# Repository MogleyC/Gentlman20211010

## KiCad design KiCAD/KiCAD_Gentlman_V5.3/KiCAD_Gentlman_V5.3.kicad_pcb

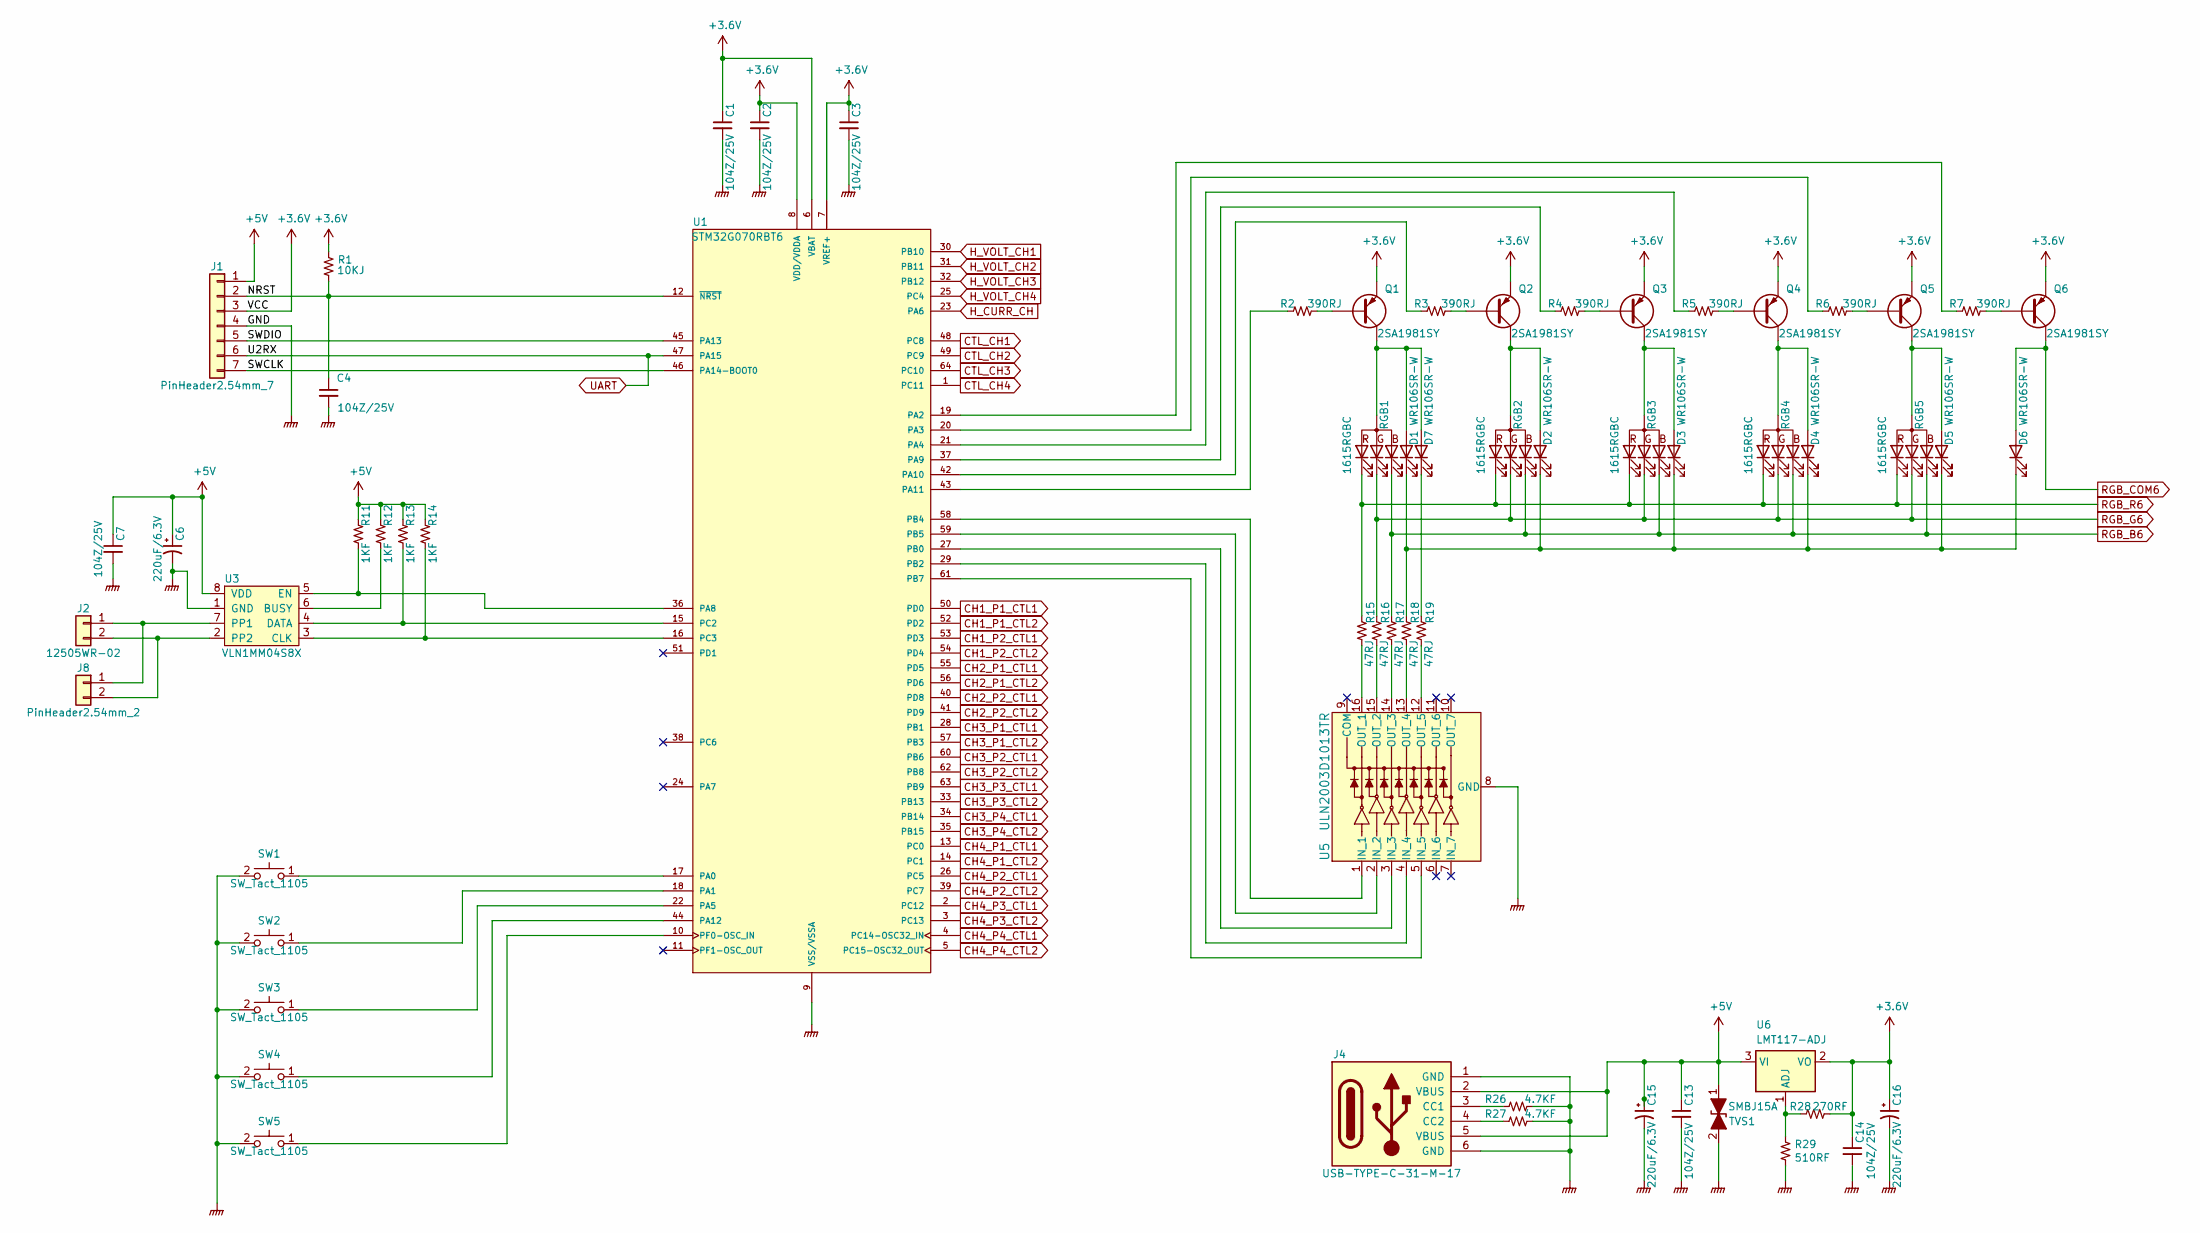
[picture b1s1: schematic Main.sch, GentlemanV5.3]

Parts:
C1, C2, C3, C4, C7, C13, C14: CAP_104Z_25V_1608; C_0603_1608Metric; PartName 104Z/25V
C6, C15, C16: CAP_220uF_6.3V_SC6.3X5.8; C_Elec_6.3x5.8; PartName 220uF/6.3V
CN1: PinHeader2.54mm_7; PinHeader_1x07_P2.54mm_Vertical; PartName PinHeader2.54mm-7P
CN2: 12505WR-02; PartName 12505WR-02
D1, D2, D3, D4, D5, D6, D7: WR106SR-W; LED_0603_1608Metric; PartName WR106SR-W
J4: USB-TYPE-C-31-M-17; TYPE-C-31-M-17-1; PartName USB-TYPE-C-31-M-17
J8: PinHeader2.54mm_2; PinHeader_1x02_P2.54mm_Vertical; PartName PinHeader2.54mm_2
Q1, Q2, Q3, Q4, Q5, Q6: 2SA1981SY; SOT-23; PartName 2SA1981SY
R1: R_10KJ; R_0603_1608Metric; PartName 10KJ
R2, R3, R4, R5, R6, R7: R_390RJ; R_0603_1608Metric; PartName 390RJ
R11, R12, R13, R14: R_1KF; R_0603_1608Metric; PartName 1KF
R15, R16, R17, R18, R19: R_47RJ; R_0603_1608Metric; PartName 47RJ
R26, R27: R_4.7KF; R_0603_1608Metric; PartName 4.7KF
R28: R_270RF; R_0603_1608Metric; PartName 270RF
R29: R_510RF; R_0603_1608Metric; PartName 510RF
RGB1, RGB2, RGB3, RGB4, RGB5: 1615RGBC; LED_RGB_0605; PartName 1615RGBC
SW1, SW2, SW3, SW4, SW5: SW_Tact_1105; SW_PUSH_6mm_H5mm; PartName ITS-1105-5mm
TVS1: SMBJ15A; D_SMB; PartName SMBJ15A
U1: STM32G070RBT6; LQFP-64_10x10mm_P0.5mm; PartName STM32G070RBT6
U3: VLN1MM04S8X; SOP-8_3.76x4.96mm_P1.27mm; PartName VLN1MM04S8X
U5: ULN2003D1013TR; SOIC-16_3.9x9.9mm_P1.27mm; PartName ULN2003D1013TR
U6: LMT117-ADJ; SOT-223-3_TabPin2; PartName LMT117-ADJ

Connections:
+3.6V: C1.1, C2.1, C3.1, C14.1, C16.1, Q1.2 (E), Q2.2 (E), Q3.2 (E), Q4.2 (E), Q5.2 (E), Q6.2 (E), R1.1, R28.1, U1.6 (VBAT), U1.7 (VREF+), U1.8 (VDD/VDDA), U6.2 (VO); also elsewhere on the board
+5V: C6.1, C7.1, C13.1, C15.1, J4.2 (VBUS), J4.5 (VBUS), R11.1, R12.1, R13.1, R14.1, TVS1.1 (A1), U3.8 (VDD), U6.3 (VI); also elsewhere on the board
/Main/NRST: C4.1, R1.2, U1.12 (~NRST); also elsewhere on the board
/Main/SWCLK: U1.46 (PA14-BOOT0); also elsewhere on the board
/Main/SWDIO: U1.45 (PA13); also elsewhere on the board
CH1_P1_CTL1: U1.50 (PD0); also elsewhere on the board
CH1_P1_CTL2: U1.52 (PD2); also elsewhere on the board
CH1_P2_CTL1: U1.53 (PD3); also elsewhere on the board
CH1_P2_CTL2: U1.54 (PD4); also elsewhere on the board
CH2_P1_CTL1: U1.55 (PD5); also elsewhere on the board
CH2_P1_CTL2: U1.56 (PD6); also elsewhere on the board
CH2_P2_CTL1: U1.40 (PD8); also elsewhere on the board
CH2_P2_CTL2: U1.41 (PD9); also elsewhere on the board
CH3_P1_CTL1: U1.28 (PB1); also elsewhere on the board
CH3_P1_CTL2: U1.57 (PB3); also elsewhere on the board
CH3_P2_CTL1: U1.60 (PB6); also elsewhere on the board
CH3_P2_CTL2: U1.62 (PB8); also elsewhere on the board
CH3_P3_CTL1: U1.63 (PB9); also elsewhere on the board
CH3_P3_CTL2: U1.33 (PB13); also elsewhere on the board
CH3_P4_CTL1: U1.34 (PB14); also elsewhere on the board
CH3_P4_CTL2: U1.35 (PB15); also elsewhere on the board
CH4_P1_CTL1: U1.13 (PC0); also elsewhere on the board
CH4_P1_CTL2: U1.14 (PC1); also elsewhere on the board
CH4_P2_CTL1: U1.26 (PC5); also elsewhere on the board
CH4_P2_CTL2: U1.39 (PC7); also elsewhere on the board
CH4_P3_CTL1: U1.2 (PC12); also elsewhere on the board
CH4_P3_CTL2: U1.3 (PC13); also elsewhere on the board
CH4_P4_CTL1: U1.4 (PC14-OSC32_IN); also elsewhere on the board
CH4_P4_CTL2: U1.5 (PC15-OSC32_OUT); also elsewhere on the board
CTL_CH1: U1.48 (PC8); also elsewhere on the board
CTL_CH2: U1.49 (PC9); also elsewhere on the board
CTL_CH3: U1.64 (PC10); also elsewhere on the board
CTL_CH4: U1.1 (PC11); also elsewhere on the board
GNDPWR: C1.2, C2.2, C3.2, C4.2, C6.2, C7.2, C13.2, C14.2, C15.2, C16.2, J4.1 (GND), J4.6 (GND), R26.1, R27.1, R29.2, SW1.2, SW2.2, SW3.2, SW4.2, SW5.2, TVS1.2 (A2), U1.9 (VSS/VSSA), U3.1 (GND), U5.8 (GND); also elsewhere on the board
H_CURR_CH: U1.23 (PA6); also elsewhere on the board
H_VOLT_CH1: U1.30 (PB10); also elsewhere on the board
H_VOLT_CH2: U1.31 (PB11); also elsewhere on the board
H_VOLT_CH3: U1.32 (PB12); also elsewhere on the board
H_VOLT_CH4: U1.25 (PC4); also elsewhere on the board
unnamed: D1.1 (K), D2.1 (K), D3.1 (K), D4.1 (K), D5.1 (K), D6.1 (K), R18.1
unnamed: D1.2 (A), D7.2 (A), Q1.3 (C), RGB1.4 (A)
unnamed: D2.2 (A), Q2.3 (C), RGB2.4 (A)
unnamed: D3.2 (A), Q3.3 (C), RGB3.4 (A)
unnamed: D4.2 (A), Q4.3 (C), RGB4.4 (A)
unnamed: D5.2 (A), Q5.3 (C), RGB5.4 (A)
unnamed: D7.1 (K), R19.1
unnamed 80: J8.1, U3.7 (PP1); also elsewhere on the board
unnamed 81: J8.2, U3.2 (PP2); also elsewhere on the board
unnamed: J4.3 (CC1), R26.2
unnamed: J4.4 (CC2), R27.2
unnamed: Q1.1 (B), R2.1
unnamed: Q2.1 (B), R3.1
unnamed: Q3.1 (B), R4.1
unnamed: Q4.1 (B), R5.1
unnamed: Q5.1 (B), R6.1
unnamed: Q6.1 (B), R7.1
unnamed: R2.2, U1.43 (PA11)
unnamed: R3.2, U1.42 (PA10)
unnamed: R4.2, U1.37 (PA9)
unnamed: R5.2, U1.21 (PA4)
unnamed: R6.2, U1.20 (PA3)
unnamed: R7.2, U1.19 (PA2)
unnamed: R11.2, U1.36 (PA8), U3.5 (EN)
unnamed: R12.2, U3.6 (BUSY)
unnamed: R13.2, U1.15 (PC2), U3.4 (DATA)
unnamed: R14.2, U1.16 (PC3), U3.3 (CLK)
unnamed: R15.2, U5.16 (OUT_1)
unnamed: R16.2, U5.15 (OUT_2)
unnamed: R17.2, U5.14 (OUT_3)
unnamed: R18.2, U5.13 (OUT_4)
unnamed: R19.2, U5.12 (OUT_5)
unnamed: R28.2, R29.1, U6.1 (ADJ)
unnamed: SW1.1, U1.17 (PA0)
unnamed: SW2.1, U1.18 (PA1)
unnamed: SW3.1, U1.22 (PA5)
unnamed: SW4.1, U1.44 (PA12)
unnamed: SW5.1, U1.10 (PF0-OSC_IN)
unnamed: U1.27 (PB0), U5.3 (IN_3)
unnamed: U1.29 (PB2), U5.4 (IN_4)
unnamed: U1.58 (PB4), U5.1 (IN_1)
unnamed: U1.59 (PB5), U5.2 (IN_2)
unnamed: U1.61 (PB7), U5.5 (IN_5)
RGB_B6: R17.1, RGB1.3 (BK), RGB2.3 (BK), RGB3.3 (BK), RGB4.3 (BK), RGB5.3 (BK); also elsewhere on the board
RGB_COM6: D6.2 (A), Q6.3 (C); also elsewhere on the board
RGB_G6: R16.1, RGB1.2 (GK), RGB2.2 (GK), RGB3.2 (GK), RGB4.2 (GK), RGB5.2 (GK); also elsewhere on the board
RGB_R6: R15.1, RGB1.1 (RK), RGB2.1 (RK), RGB3.1 (RK), RGB4.1 (RK), RGB5.1 (RK); also elsewhere on the board
UART: U1.47 (PA15); also elsewhere on the board

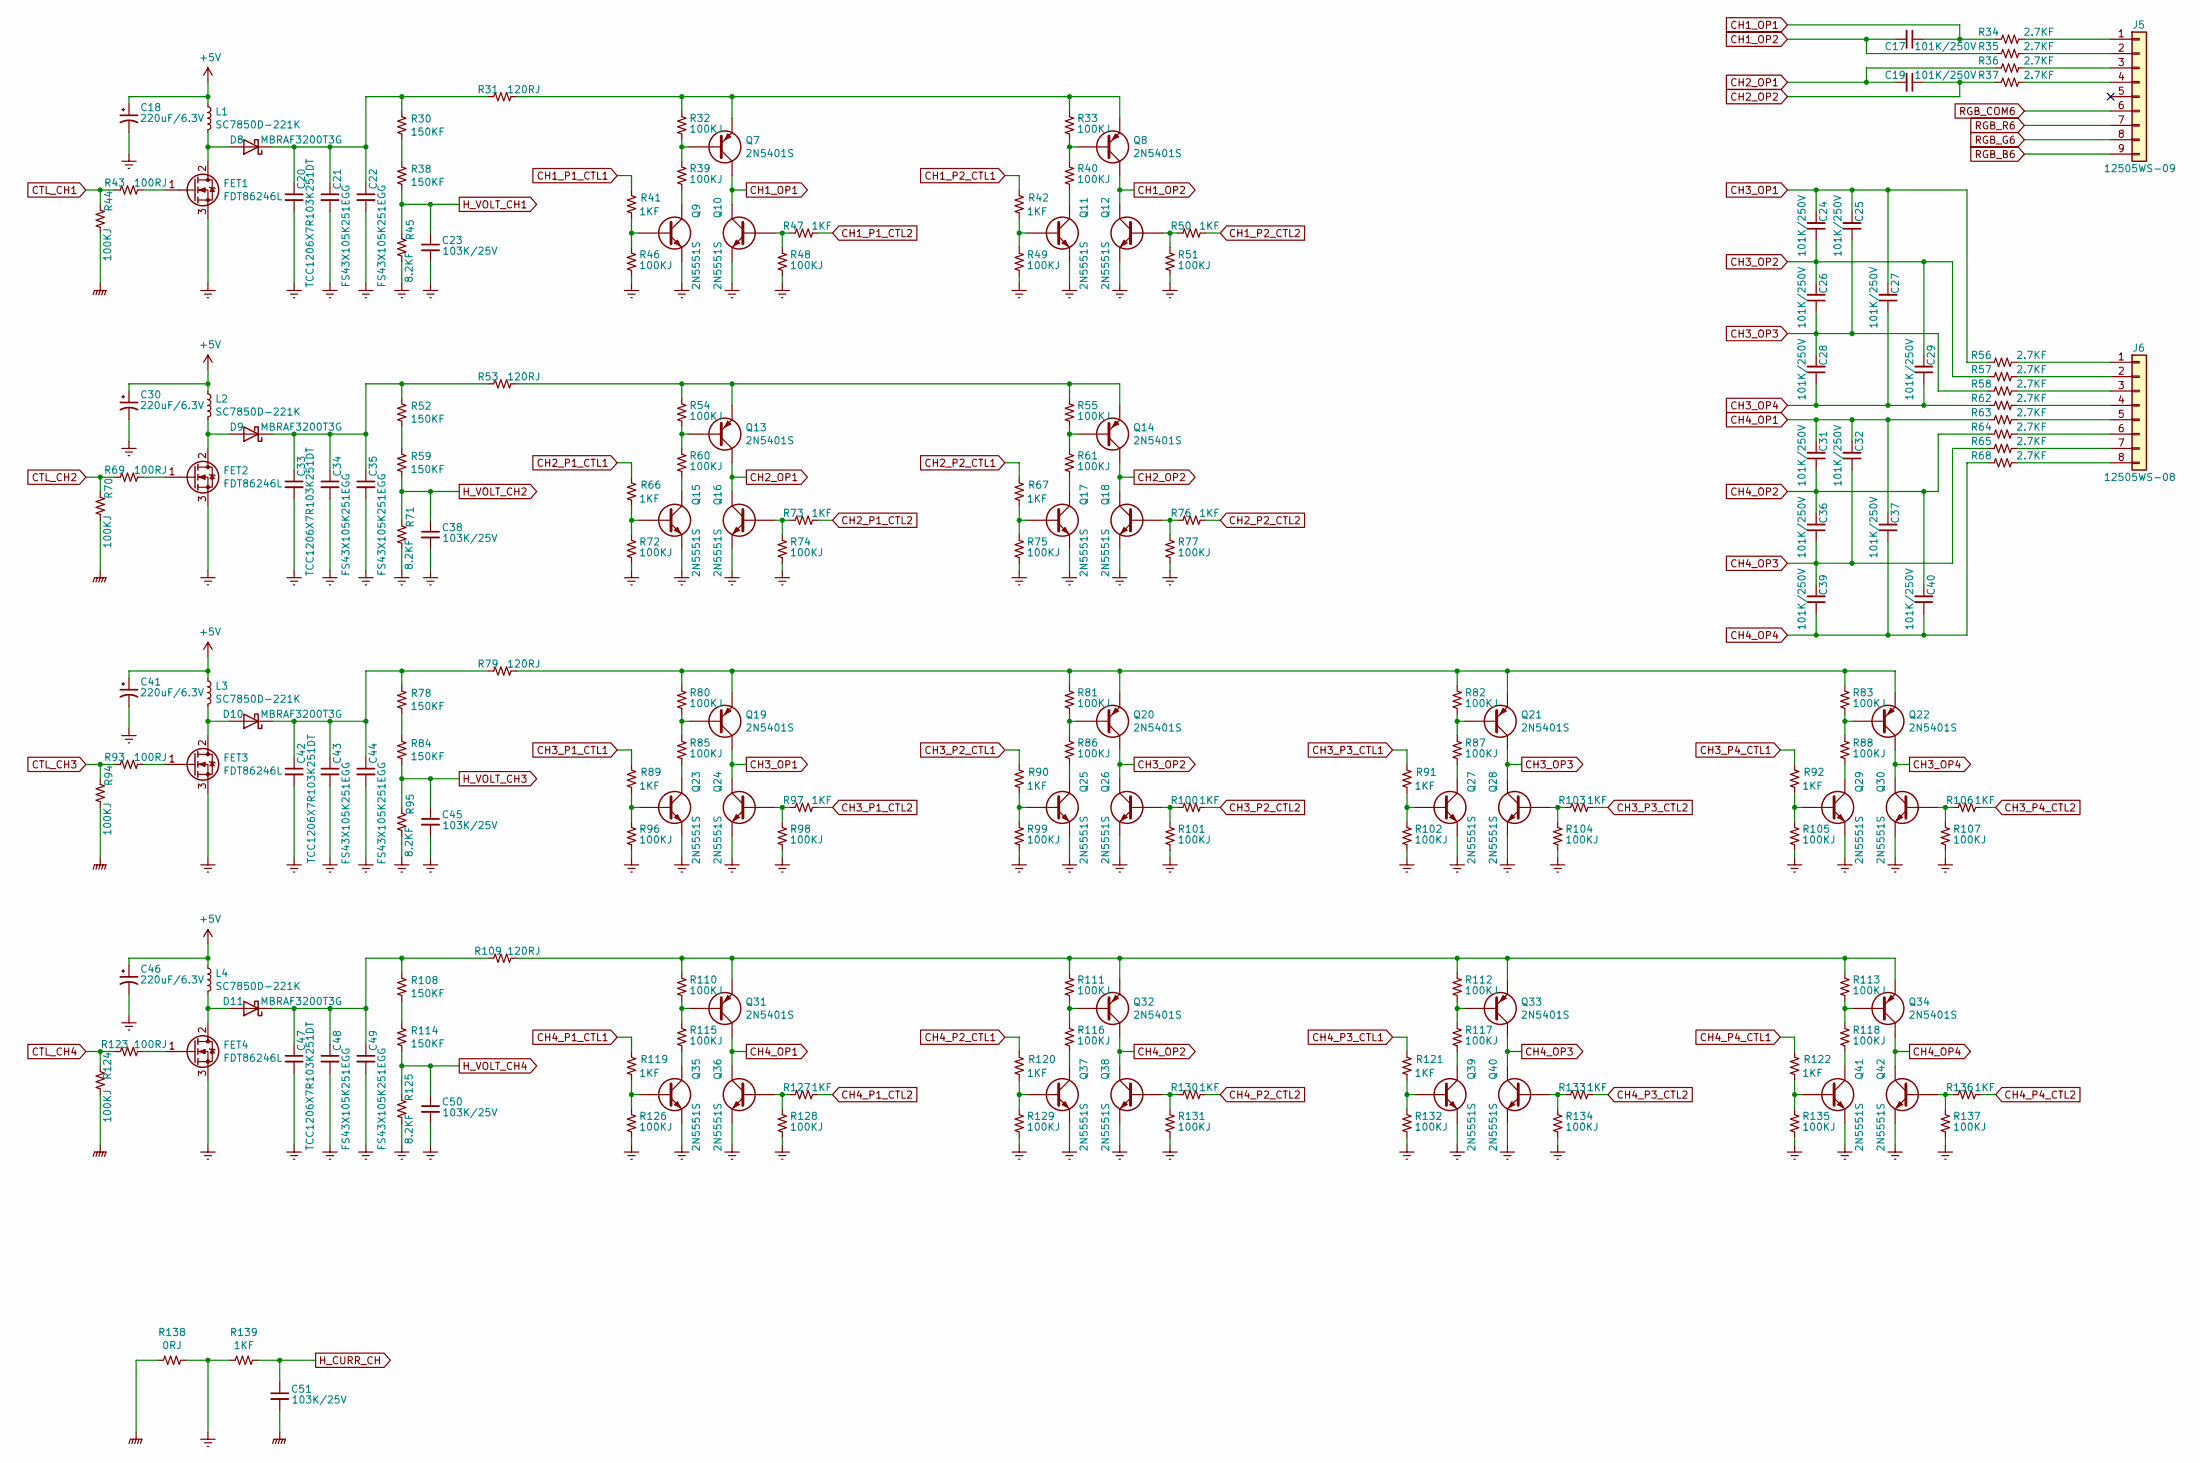
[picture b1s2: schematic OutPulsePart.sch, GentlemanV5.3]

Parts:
C17, C19, C24, C25, C26, C27, C28, C29, C31, C32, C36, C37, C39, C40: CAP_101K_250V_2012; C_0805_2012Metric; PartName 101K/250V
C18, C30, C41, C46: CAP_220uF_6.3V_SC6.3X5.8; C_Elec_6.3x5.8; PartName 220uF/6.3V
C20, C33, C42, C47: CAP_103K_250V_3216; C_1206_3216Metric; PartName TCC1206X7R103K251DT
C21, C22, C34, C35, C43, C44, C48, C49: CAP_105K_250V_4532; C_1812_4532Metric; PartName FS43X105K251EGG
C23, C38, C45, C50, C51: CAP_103K_25V_1608; C_0603_1608Metric; PartName 103K/25V
D8, D9, D10, D11: MBRAF3200T3G; D_SMA; PartName MBRAF3200T3G
FET1, FET2, FET3, FET4: FDT86246L; SOT-223-3_TabPin2; PartName FDT86246L
J5: 12505WS-09; PartName 12505WS-09
J6: 12505WS-08; PartName 12505WS-08
L1, L2, L3, L4: SC7850D-221K; L_SC7850D-221K; PartName SC7850D-221K
Q7, Q8, Q13, Q14, Q19, Q20, Q21, Q22, Q31, Q32, Q33, Q34: 2N5401S; SOT-23; PartName 2N5401S
Q9, Q10, Q11, Q12, Q15, Q16, Q17, Q18, Q23, Q24, Q25, Q26, Q27, Q28, Q29, Q30, Q35, Q36, Q37, Q38, Q39, Q40, Q41, Q42: 2N5551S; SOT-23; PartName 2N5551S
R30, R38, R52, R59, R78, R84, R108, R114: R_150KF_2012; R_0805_2012Metric; PartName 150KF
R31, R53, R79, R109: R_120RJ_3216; R_1206_3216Metric; PartName 120RJ
R32, R33, R39, R40, R44, R46, R48, R49, R51, R54, R55, R60, R61, R70, R72, R74, R75, R77, R80, R81, R82, R83, R85, R86, R87, R88, R94, R96, R98, R99, R101, R102, R104, R105, R107, R110, R111, R112, R113, R115, R116, R117, R118, R124, R126, R128, R129, R131, R132, R134, R135, R137: R_100KJ; R_0603_1608Metric; PartName 100KJ
R34, R35, R36, R37, R56, R57, R58, R62, R63, R64, R65, R68: R_2.7KF; R_0603_1608Metric; PartName 2.7KF
R41, R42, R47, R50, R66, R67, R73, R76, R89, R90, R91, R92, R97, R100, R103, R106, R119, R120, R121, R122, R127, R130, R133, R136, R139: R_1KF; R_0603_1608Metric; PartName 1KF
R43, R69, R93, R123: R_100RJ; R_0603_1608Metric; PartName 100RJ
R45, R71, R95, R125: R_8.2KF; R_0603_1608Metric; PartName 8.2KF
R138: R_0RJ_6432; R_3522_6432Metric; PartName 0RJ

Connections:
+5V: C18.1, C30.1, C41.1, C46.1, L1.1, L2.1, L3.1, L4.1; also elsewhere on the board
CH1_OP1: C17.1, Q7.3 (C), Q10.3 (C), R34.2
CH1_OP2: C17.2, Q8.3 (C), Q12.3 (C), R35.2
CH1_P1_CTL1: R41.1; also elsewhere on the board
CH1_P1_CTL2: R47.1; also elsewhere on the board
CH1_P2_CTL1: R42.1; also elsewhere on the board
CH1_P2_CTL2: R50.1; also elsewhere on the board
CH2_OP1: C19.2, Q13.3 (C), Q16.3 (C), R36.2
CH2_OP2: C19.1, Q14.3 (C), Q18.3 (C), R37.2
CH2_P1_CTL1: R66.1; also elsewhere on the board
CH2_P1_CTL2: R73.1; also elsewhere on the board
CH2_P2_CTL1: R67.1; also elsewhere on the board
CH2_P2_CTL2: R76.1; also elsewhere on the board
CH3_OP1: C24.2, C25.2, C27.2, Q19.3 (C), Q24.3 (C), R56.2
CH3_OP2: C24.1, C26.2, C29.2, Q20.3 (C), Q26.3 (C), R57.2
CH3_OP3: C25.1, C26.1, C28.2, Q21.3 (C), Q28.3 (C), R58.2
CH3_OP4: C27.1, C28.1, C29.1, Q22.3 (C), Q30.3 (C), R62.2
CH3_P1_CTL1: R89.1; also elsewhere on the board
CH3_P1_CTL2: R97.1; also elsewhere on the board
CH3_P2_CTL1: R90.1; also elsewhere on the board
CH3_P2_CTL2: R100.1; also elsewhere on the board
CH3_P3_CTL1: R91.1; also elsewhere on the board
CH3_P3_CTL2: R103.1; also elsewhere on the board
CH3_P4_CTL1: R92.1; also elsewhere on the board
CH3_P4_CTL2: R106.1; also elsewhere on the board
CH4_OP1: C31.2, C32.2, C37.2, Q31.3 (C), Q36.3 (C), R63.2
CH4_OP2: C31.1, C36.2, C40.2, Q32.3 (C), Q38.3 (C), R64.2
CH4_OP3: C32.1, C36.1, C39.2, Q33.3 (C), Q40.3 (C), R65.2
CH4_OP4: C37.1, C39.1, C40.1, Q34.3 (C), Q42.3 (C), R68.2
CH4_P1_CTL1: R119.1; also elsewhere on the board
CH4_P1_CTL2: R127.1; also elsewhere on the board
CH4_P2_CTL1: R120.1; also elsewhere on the board
CH4_P2_CTL2: R130.1; also elsewhere on the board
CH4_P3_CTL1: R121.1; also elsewhere on the board
CH4_P3_CTL2: R133.1; also elsewhere on the board
CH4_P4_CTL1: R122.1; also elsewhere on the board
CH4_P4_CTL2: R136.1; also elsewhere on the board
CTL_CH1: R43.2, R44.1; also elsewhere on the board
CTL_CH2: R69.2, R70.1; also elsewhere on the board
CTL_CH3: R93.2, R94.1; also elsewhere on the board
CTL_CH4: R123.2, R124.1; also elsewhere on the board
GNDPWR: C51.2, R44.2, R70.2, R94.2, R124.2, R138.2; also elsewhere on the board
GNDREF: C18.2, C20.2, C21.2, C22.2, C23.2, C30.2, C33.2, C34.2, C35.2, C38.2, C41.2, C42.2, C43.2, C44.2, C45.2, C46.2, C47.2, C48.2, C49.2, C50.2, FET1.3 (S), FET2.3 (S), FET3.3 (S), FET4.3 (S), Q9.2 (E), Q10.2 (E), Q11.2 (E), Q12.2 (E), Q15.2 (E), Q16.2 (E), Q17.2 (E), Q18.2 (E), Q23.2 (E), Q24.2 (E), Q25.2 (E), Q26.2 (E), Q27.2 (E), Q28.2 (E), Q29.2 (E), Q30.2 (E), Q35.2 (E), Q36.2 (E), Q37.2 (E), Q38.2 (E), Q39.2 (E), Q40.2 (E), Q41.2 (E), Q42.2 (E), R45.2, R46.2, R48.2, R49.2, R51.2, R71.2, R72.2, R74.2, R75.2, R77.2, R95.2, R96.2, R98.2, R99.2, R101.2, R102.2, R104.2, R105.2, R107.2, R125.2, R126.2, R128.2, R129.2, R131.2, R132.2, R134.2, R135.2, R137.2, R138.1, R139.2
H_CURR_CH: C51.1, R139.1; also elsewhere on the board
H_VOLT_CH1: C23.1, R38.2, R45.1; also elsewhere on the board
H_VOLT_CH2: C38.1, R59.2, R71.1; also elsewhere on the board
H_VOLT_CH3: C45.1, R84.2, R95.1; also elsewhere on the board
H_VOLT_CH4: C50.1, R114.2, R125.1; also elsewhere on the board
unnamed: C20.1, C21.1, C22.1, D8.1 (K), R30.1, R31.2
unnamed: C33.1, C34.1, C35.1, D9.1 (K), R52.1, R53.2
unnamed: C42.1, C43.1, C44.1, D10.1 (K), R78.1, R79.2
unnamed: C47.1, C48.1, C49.1, D11.1 (K), R108.1, R109.2
unnamed: D8.2 (A), FET1.2 (D), L1.2
unnamed: D9.2 (A), FET2.2 (D), L2.2
unnamed: D10.2 (A), FET3.2 (D), L3.2
unnamed: D11.2 (A), FET4.2 (D), L4.2
unnamed: FET1.1 (G), R43.1
unnamed: FET2.1 (G), R69.1
unnamed: FET3.1 (G), R93.1
unnamed: FET4.1 (G), R123.1
unnamed: J5.1, R34.1
unnamed: J5.2, R35.1
unnamed: J5.3, R36.1
unnamed: J5.4, R37.1
unnamed: J6.1, R56.1
unnamed: J6.2, R57.1
unnamed: J6.3, R58.1
unnamed: J6.4, R62.1
unnamed: J6.5, R63.1
unnamed: J6.6, R64.1
unnamed: J6.7, R65.1
unnamed: J6.8, R68.1
unnamed: Q7.1 (B), R32.2, R39.1
unnamed: Q7.2 (E), Q8.2 (E), R31.1, R32.1, R33.1
unnamed: Q8.1 (B), R33.2, R40.1
unnamed: Q9.1 (B), R41.2, R46.1
unnamed: Q9.3 (C), R39.2
unnamed: Q10.1 (B), R47.2, R48.1
unnamed: Q11.1 (B), R42.2, R49.1
unnamed: Q11.3 (C), R40.2
unnamed: Q12.1 (B), R50.2, R51.1
unnamed: Q13.1 (B), R54.2, R60.1
unnamed: Q13.2 (E), Q14.2 (E), R53.1, R54.1, R55.1
unnamed: Q14.1 (B), R55.2, R61.1
unnamed: Q15.1 (B), R66.2, R72.1
unnamed: Q15.3 (C), R60.2
unnamed: Q16.1 (B), R73.2, R74.1
unnamed: Q17.1 (B), R67.2, R75.1
unnamed: Q17.3 (C), R61.2
unnamed: Q18.1 (B), R76.2, R77.1
unnamed: Q19.1 (B), R80.2, R85.1
unnamed: Q19.2 (E), Q20.2 (E), Q21.2 (E), Q22.2 (E), R79.1, R80.1, R81.1, R82.1, R83.1
unnamed: Q20.1 (B), R81.2, R86.1
unnamed: Q21.1 (B), R82.2, R87.1
unnamed: Q22.1 (B), R83.2, R88.1
unnamed: Q23.1 (B), R89.2, R96.1
unnamed: Q23.3 (C), R85.2
unnamed: Q24.1 (B), R97.2, R98.1
unnamed: Q25.1 (B), R90.2, R99.1
unnamed: Q25.3 (C), R86.2
unnamed: Q26.1 (B), R100.2, R101.1
unnamed: Q27.1 (B), R91.2, R102.1
unnamed: Q27.3 (C), R87.2
unnamed: Q28.1 (B), R103.2, R104.1
unnamed: Q29.1 (B), R92.2, R105.1
unnamed: Q29.3 (C), R88.2
unnamed: Q30.1 (B), R106.2, R107.1
unnamed: Q31.1 (B), R110.2, R115.1
unnamed: Q31.2 (E), Q32.2 (E), Q33.2 (E), Q34.2 (E), R109.1, R110.1, R111.1, R112.1, R113.1
unnamed: Q32.1 (B), R111.2, R116.1
unnamed: Q33.1 (B), R112.2, R117.1
unnamed: Q34.1 (B), R113.2, R118.1
unnamed: Q35.1 (B), R119.2, R126.1
unnamed: Q35.3 (C), R115.2
unnamed: Q36.1 (B), R127.2, R128.1
unnamed: Q37.1 (B), R120.2, R129.1
unnamed: Q37.3 (C), R116.2
unnamed: Q38.1 (B), R130.2, R131.1
unnamed: Q39.1 (B), R121.2, R132.1
unnamed: Q39.3 (C), R117.2
unnamed: Q40.1 (B), R133.2, R134.1
unnamed: Q41.1 (B), R122.2, R135.1
unnamed: Q41.3 (C), R118.2
unnamed: Q42.1 (B), R136.2, R137.1
unnamed: R30.2, R38.1
unnamed: R52.2, R59.1
unnamed: R78.2, R84.1
unnamed: R108.2, R114.1
RGB_B6: J5.9; also elsewhere on the board
RGB_COM6: J5.6; also elsewhere on the board
RGB_G6: J5.8; also elsewhere on the board
RGB_R6: J5.7; also elsewhere on the board

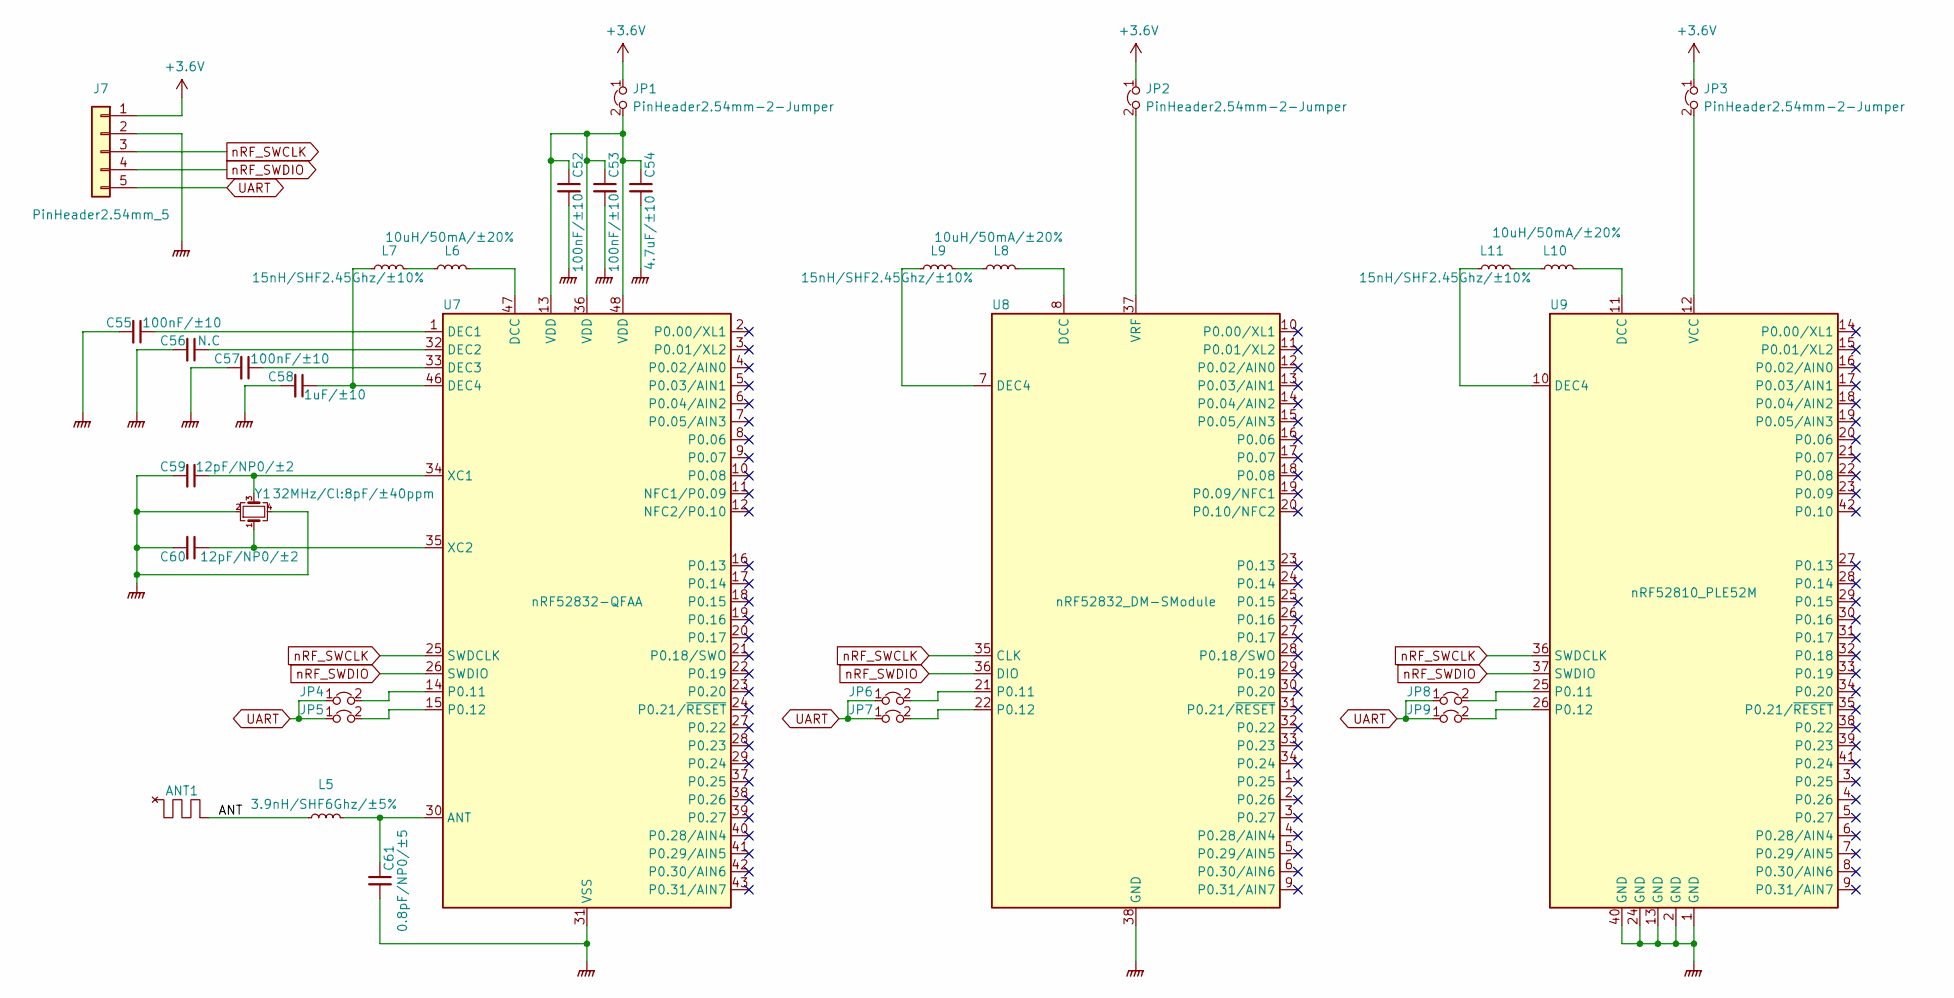
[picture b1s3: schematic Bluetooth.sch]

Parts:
ANT1: ANT; ANT_PATTERN
C52, C53, C55, C57: CAP_100nF_1005; C_0402_1005Metric; PartName 100nF/±10
C54: CAP_4.7uF_1005; C_0402_1005Metric; PartName 4.7uF/±10
C56: CAP_N.C_1005; C_0402_1005Metric; PartName N.C
C58: CAP_1uF_1005; C_0402_1005Metric; PartName 1uF/±10
C59, C60: CAP_12pF_1005; C_0402_1005Metric; PartName 12pF/NP0/±2
C61: CAP_0.8pF_1005; C_0402_1005Metric; PartName 0.8pF/NP0/±5
J7: PinHeader2.54mm_5; PinHeader_1x05_P2.54mm_Vertical; PartName PinHeader2.54mm-5P
JP1, JP2, JP3, JP4, JP5, JP6, JP7, JP8, JP9: PinHeader2.54mm-2-Jumper; PinHeader_1x02_P2.54mm_Vertical; PartName PinHeader2.54mm-2-Jumper
L5: L_3.9nH; L_0402_1005Metric; PartName 3.9nH/SHF6Ghz/±5%
L6, L8, L10: L_10uH; L_0603_1608Metric; PartName 10uH/50mA/±20%
L7, L9, L11: L_15nH; L_0402_1005Metric; PartName 15nH/SHF2.45Ghz/±10%
U7: nRF52832-QFAA; QFN-48-1EP_6x6mm_P0.4mm_EP4.3x4.3mm; PartName nRF52832-QFAA
U8: nRF52832_DM-SModule; PartName nRF52832_DM-SModule
U9: nRF52810_PLE52M; PartName nRF52810_PLE52M
Y1: Y_32MHz; Crystal_SMD_2016-4Pin_2.0x1.6mm; PartName 32MHz/Cl:8pF/±40ppm

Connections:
+3.6V: J7.1, JP1.1, JP2.1, JP3.1; also elsewhere on the board
/Bluetooth/ANT: ANT1.1, L5.1
GNDPWR: C52.2, C53.2, C54.2, C55.2, C56.2, C57.2, C58.2, C59.2, C60.2, C61.2, J7.2, U7.31 (VSS), U7.45 (VSS), U7.49 (VSS), U8.38 (GND), U9.1 (GND), U9.2 (GND), U9.13 (GND), U9.24 (GND), U9.40 (GND), Y1.2, Y1.4; also elsewhere on the board
unnamed: C52.1, C53.1, C54.1, JP1.2, U7.13 (VDD), U7.36 (VDD), U7.48 (VDD)
unnamed: C55.1, U7.1 (DEC1)
unnamed: C56.1, U7.32 (DEC2)
unnamed: C57.1, U7.33 (DEC3)
unnamed: C58.1, L7.1, U7.46 (DEC4)
unnamed: C59.1, U7.34 (XC1), Y1.3
unnamed: C60.1, U7.35 (XC2), Y1.1
unnamed: C61.1, L5.2, U7.30 (ANT)
unnamed: JP2.2, U8.37 (VRF)
unnamed: JP3.2, U9.12 (VCC)
unnamed: JP4.2, U7.14 (P0.11)
unnamed: JP5.2, U7.15 (P0.12)
unnamed: JP6.2, U8.21 (P0.11)
unnamed: JP7.2, U8.22 (P0.12)
unnamed: JP8.2, U9.25 (P0.11)
unnamed: JP9.2, U9.26 (P0.12)
unnamed: L6.1, L7.2
unnamed: L6.2, U7.47 (DCC)
unnamed: L8.1, L9.2
unnamed: L8.2, U8.8 (DCC)
unnamed: L9.1, U8.7 (DEC4)
unnamed: L10.1, L11.2
unnamed: L10.2, U9.11 (DCC)
unnamed: L11.1, U9.10 (DEC4)
UART: J7.5, JP4.1, JP5.1, JP6.1, JP7.1, JP8.1, JP9.1; also elsewhere on the board
nRF_SWCLK: J7.3, U7.25 (SWDCLK), U8.35 (CLK), U9.36 (SWDCLK)
nRF_SWDIO: J7.4, U7.26 (SWDIO), U8.36 (DIO), U9.37 (SWDIO)
